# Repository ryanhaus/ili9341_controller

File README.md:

# ili9341_controller
Powered by an RP2040 and a Lattice iCE40UP5K, made by Ryan Hausmann.
Please note that everything was tested on Ubuntu running on Windows through WSL.

## Block diagram

Please note that this design has not been tested on actual hardware yet.

## Prerequisites
Run `sudo apt install make cmake gcc-arm-none-eabi libnewlib-arm-none-eabi libstdc++-arm-none-eabi-newlib build-essential clang bison flex libreadline-dev gawk tcl-dev libffi-dev git mercurial graphviz xdot pkg-config python3 libftdi-dev qtbase5-dev qtchooser qt5-qmake qtbase5-dev-tools python3-dev libboost-all-dev cmake libeigen3-dev git help2man perl python3 g++ verilator libsdl2-dev libsdl2-2.0-0`.
This is enough to do simulation with Verilator and SDL. To install the synthesis tools and the Pico SDK, run `./install_synthesis.sh`.

## Synthesis/Pico Build
Synthesis is handled by Yosys and Project Icestorm. The Pico firmware is compiled using cmake & pico-sdk.
### Building
The FPGA configuration is packaged into the RP2040 program. The `build/ili9341_controller.uf2` file can be built with `make` or `make pico`. This will compile the RP2040 program and also automatically build the FPGA configuration, with the files stored in the `build` directory. 
### Programming
On Windows, the generated uf2 file can be dragged into the Pico's drive folder.

## Simulation
Simulation has been implemented with Verilog and SDL.
### Building
To build the simulation program, run `make verilator`.
### Running
To run the simulation program, run `./build/Vili9341_controller`. The program will not do anything useful by default, but all the options can be viewed with the `--help` argument.
### Screen Simulation
To show the simulated screen output, run `./build/Vili9341_controller --screen-sim`. The `--screen-scale` argument can also be used to scale the screen, the default is 1x (240x320 px).
Below is a screenshot of a simulation with letter sprites:

## Cleaning
`make clean` will remove all build files. The dependencies will remain in the `dep` folder.

## Hardware (WIP)
All KiCad files for the PCB are in the `pcb` folder. Click [here](./pcb/sch.pdf) to download the current schematic as a PDF (`pcb/sch.pdf`).
Top view of current PCB design:

Bottom view of current PCB design:

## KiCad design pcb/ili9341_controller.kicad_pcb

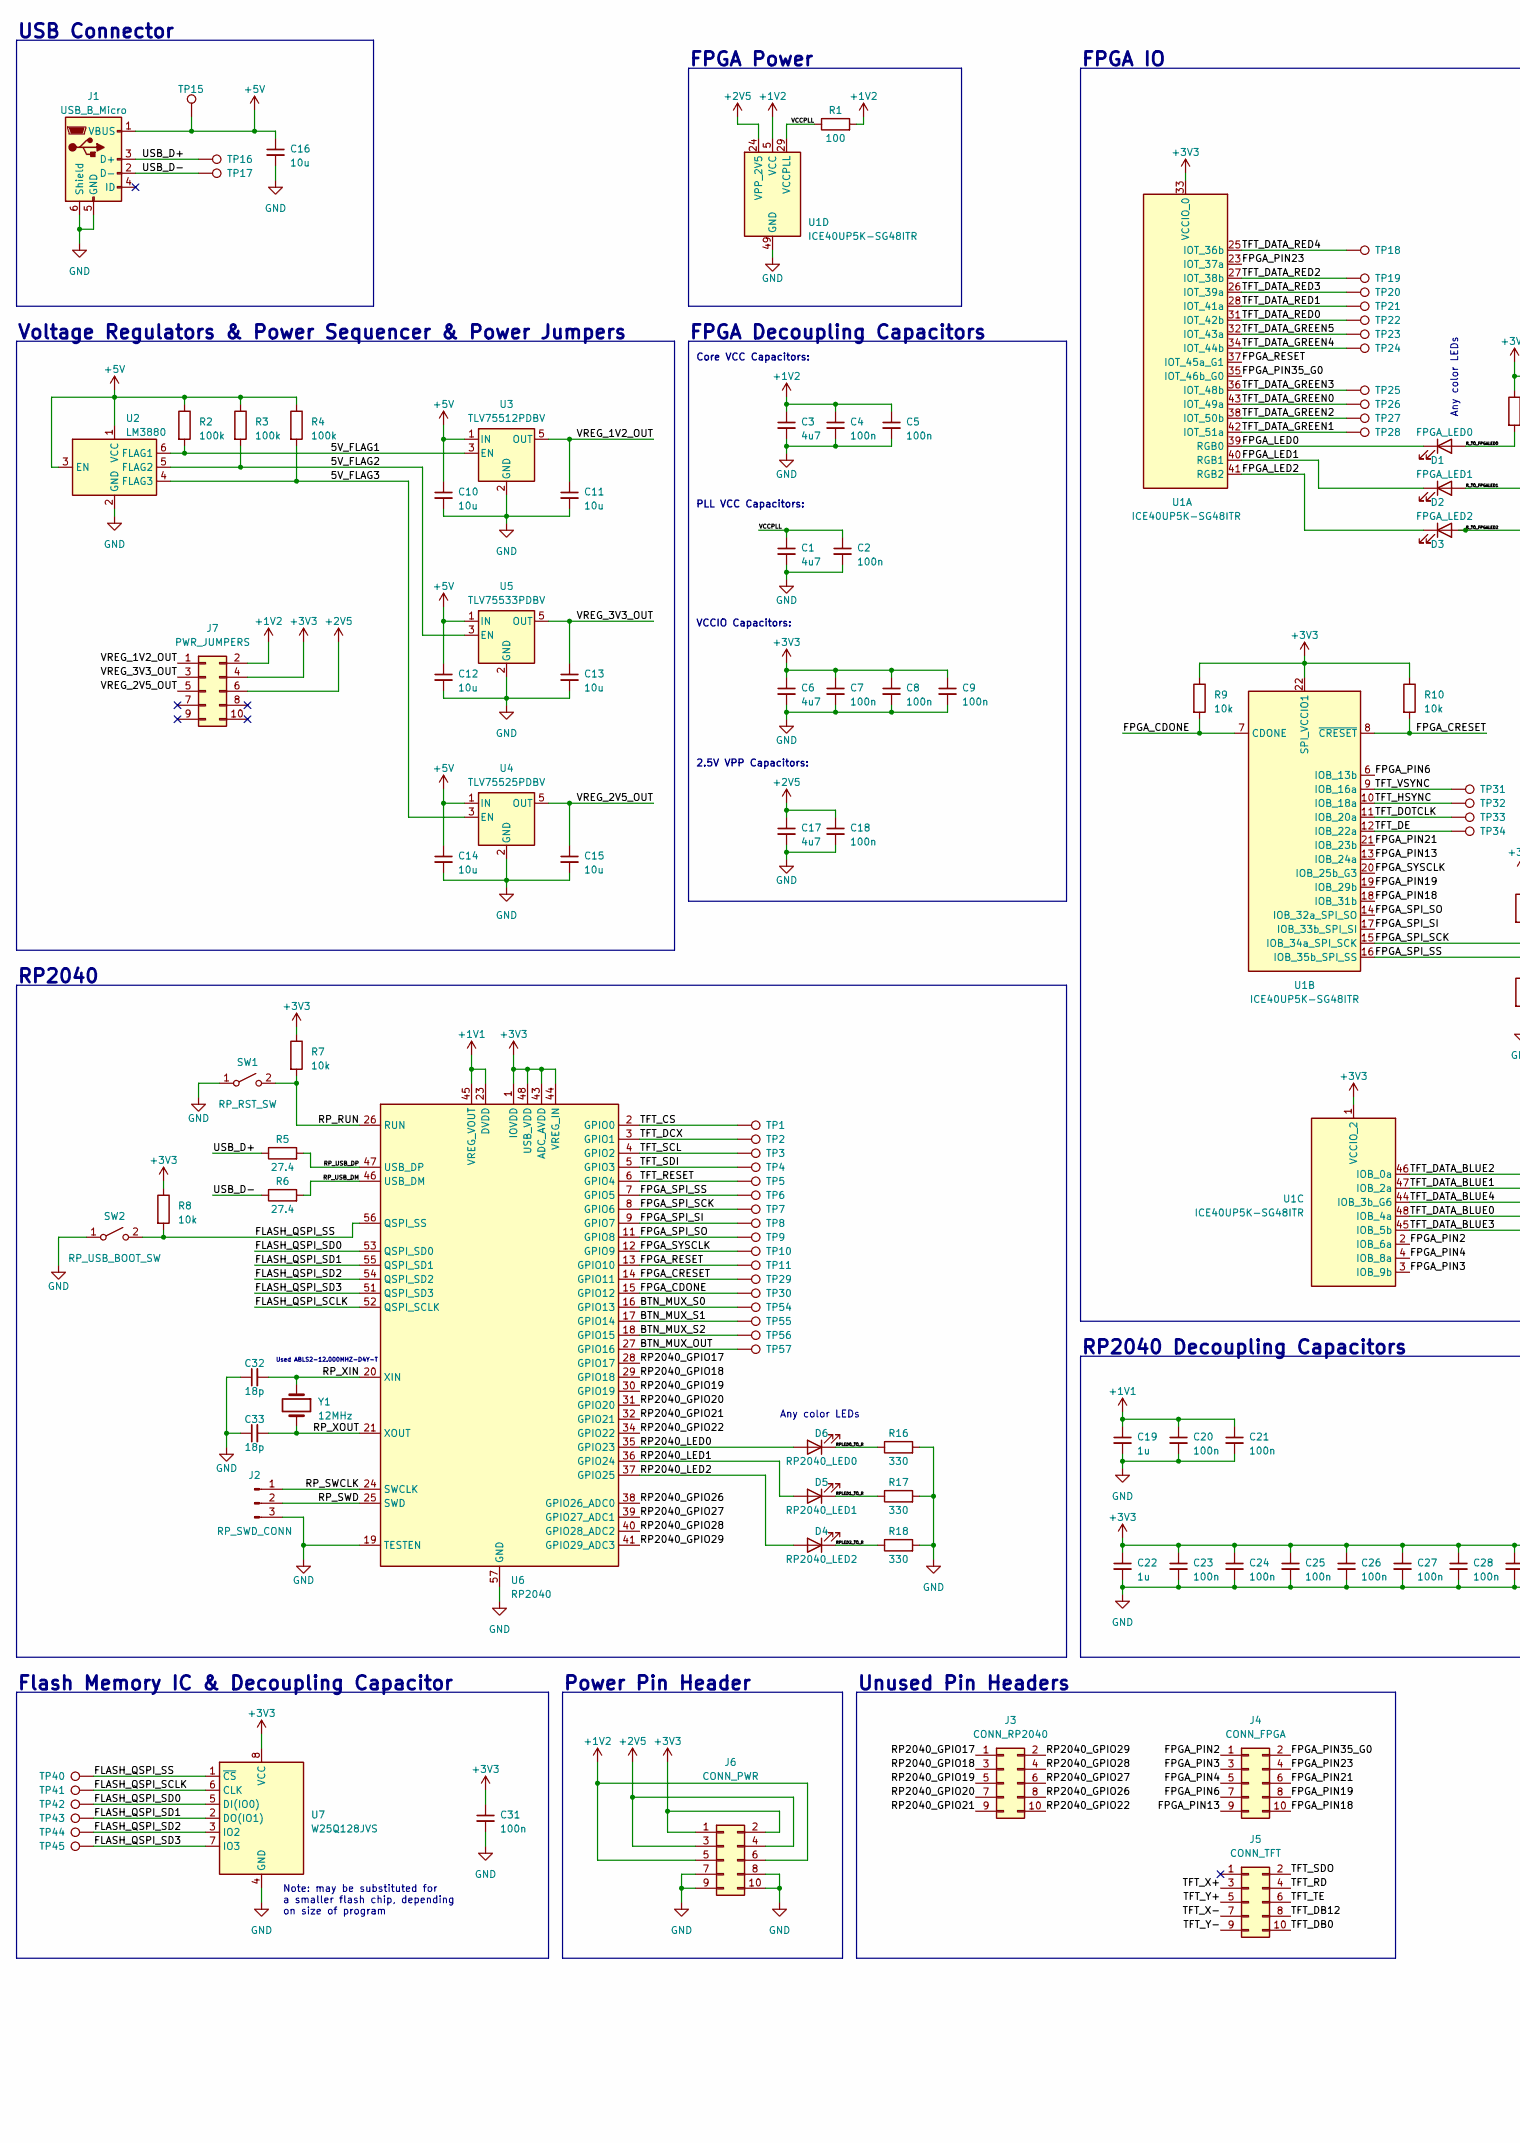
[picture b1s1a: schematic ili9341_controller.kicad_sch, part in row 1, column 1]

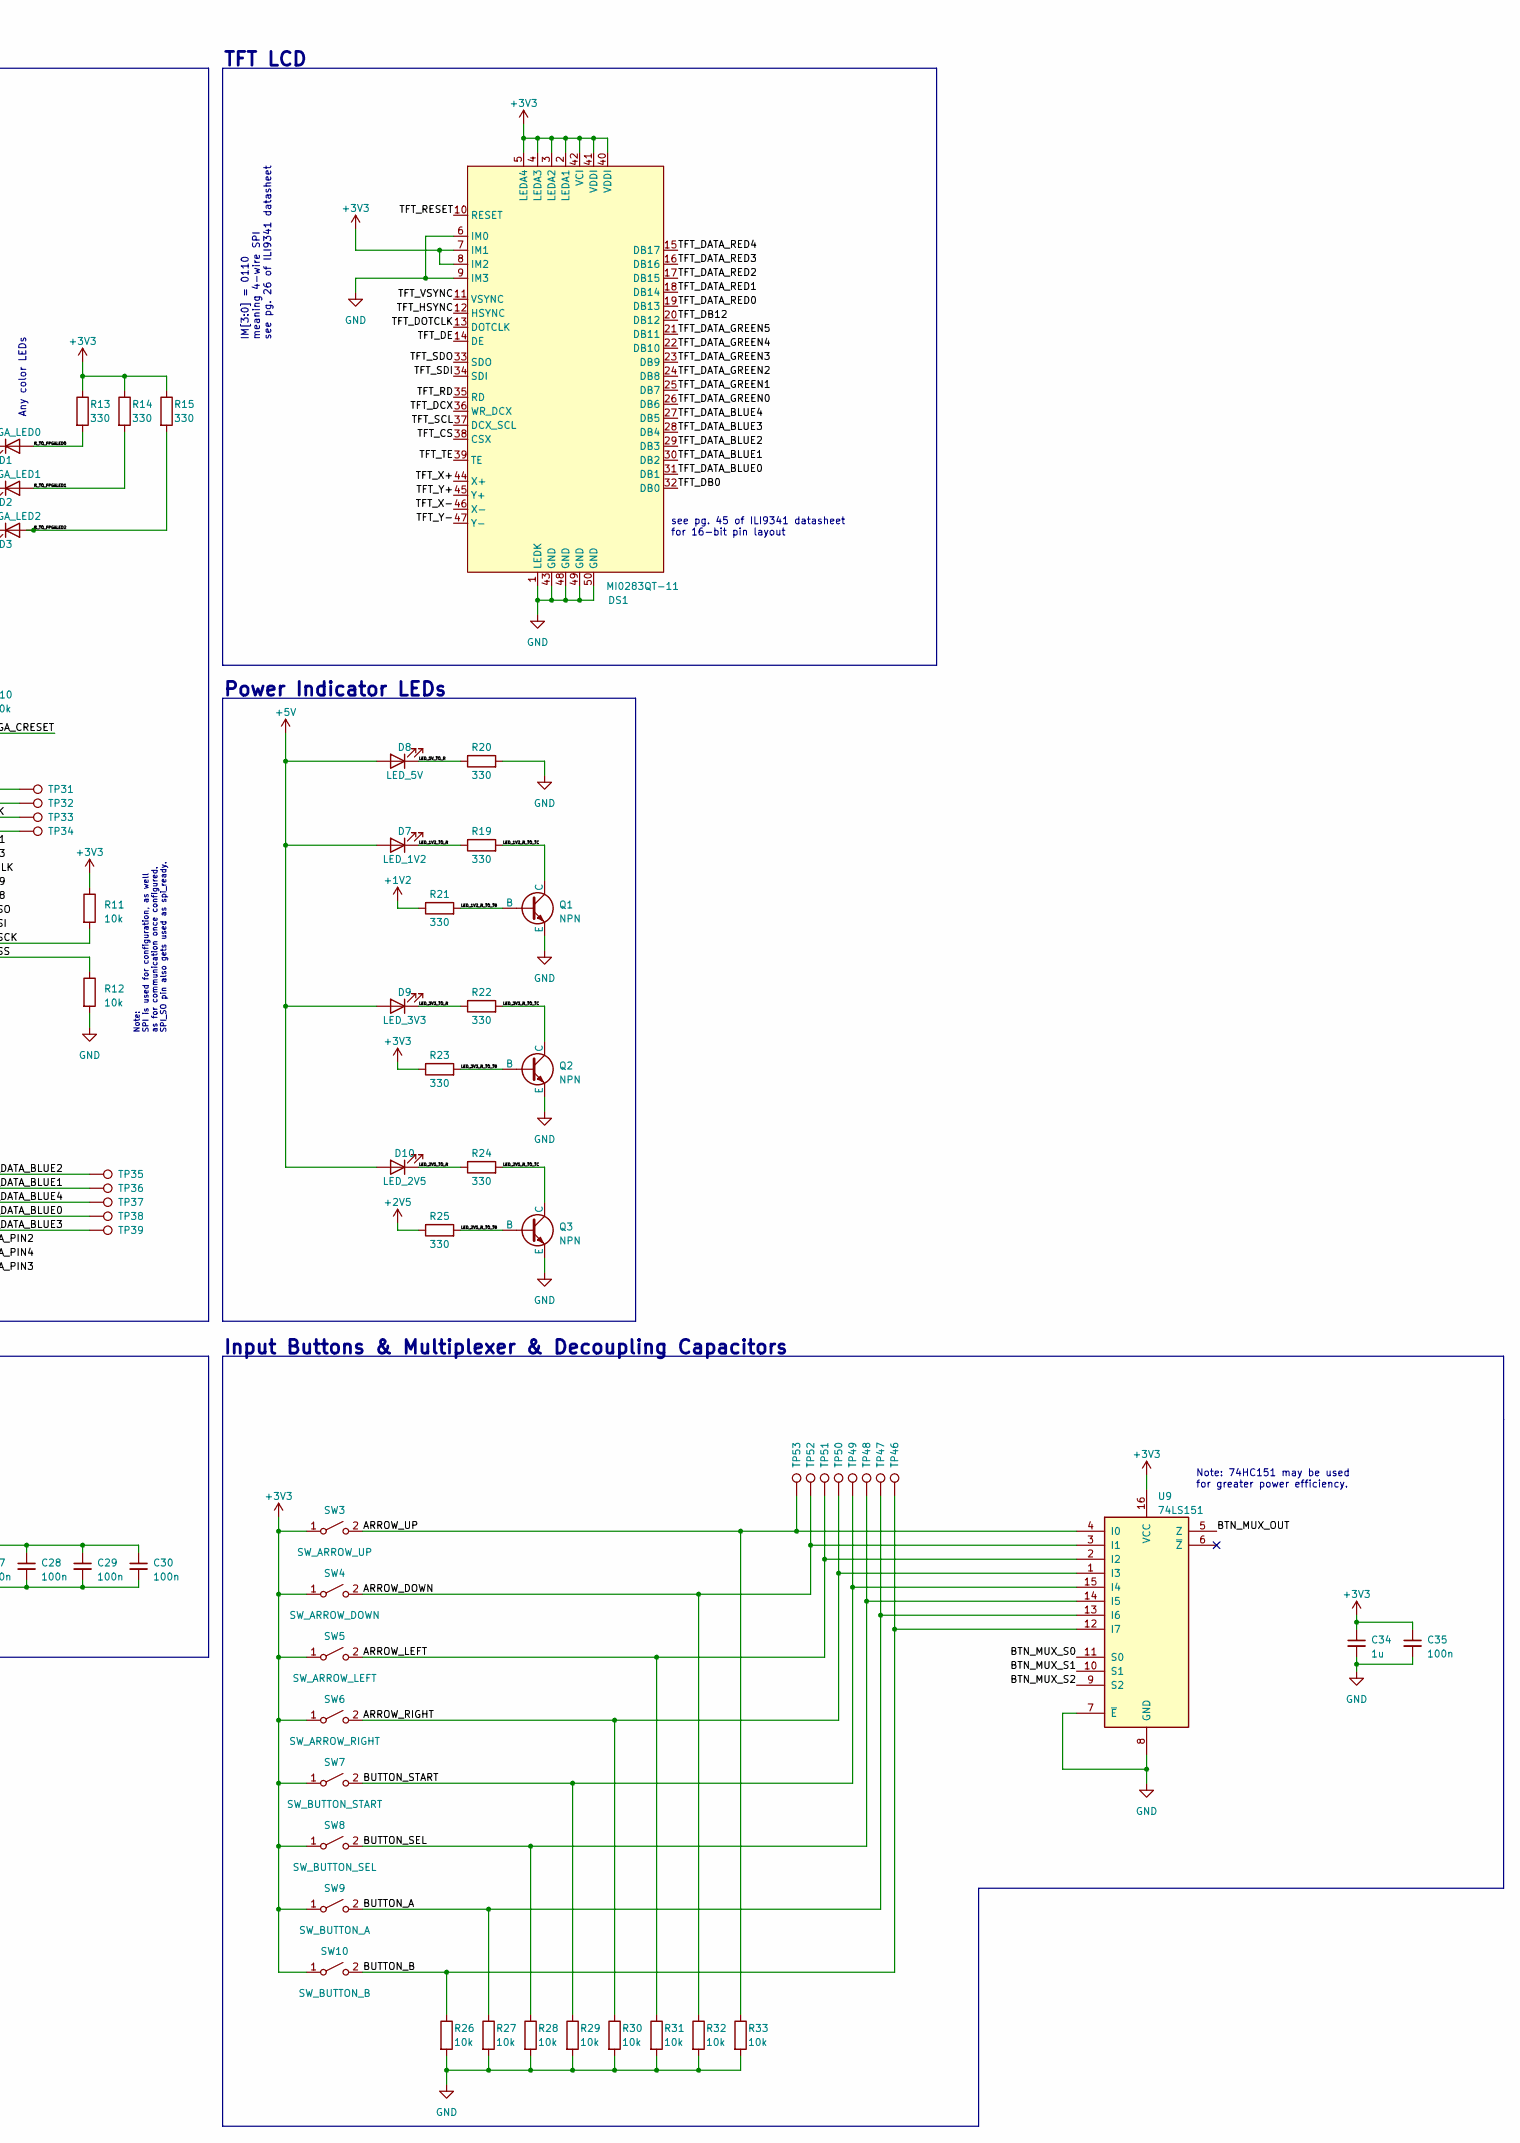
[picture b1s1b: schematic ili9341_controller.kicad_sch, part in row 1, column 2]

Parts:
C1, C3, C6, C17: 4u7; C_0603_1608Metric_Pad1.08x0.95mm_HandSolder
C2, C4, C5, C7, C8, C9, C18, C20, C21, C23, C24, C25, C26, C27, C28, C29, C30, C31, C35: 100n; C_0603_1608Metric_Pad1.08x0.95mm_HandSolder
C10, C11, C12, C13, C14, C15, C16: 10u; C_0603_1608Metric_Pad1.08x0.95mm_HandSolder
C19, C22, C34: 1u; C_0603_1608Metric_Pad1.08x0.95mm_HandSolder
C32, C33: 18p; C_0603_1608Metric_Pad1.08x0.95mm_HandSolder
D1: FPGA_LED0; LED_0603_1608Metric_Pad1.05x0.95mm_HandSolder
D2: FPGA_LED1; LED_0603_1608Metric_Pad1.05x0.95mm_HandSolder
D3: FPGA_LED2; LED_0603_1608Metric_Pad1.05x0.95mm_HandSolder
D4: RP2040_LED2; LED_0603_1608Metric_Pad1.05x0.95mm_HandSolder
D5: RP2040_LED1; LED_0603_1608Metric_Pad1.05x0.95mm_HandSolder
D6: RP2040_LED0; LED_0603_1608Metric_Pad1.05x0.95mm_HandSolder
D7: LED_1V2; LED_0603_1608Metric_Pad1.05x0.95mm_HandSolder
D8: LED_5V; LED_0603_1608Metric_Pad1.05x0.95mm_HandSolder
D9: LED_3V3; LED_0603_1608Metric_Pad1.05x0.95mm_HandSolder
D10: LED_2V5; LED_0603_1608Metric_Pad1.05x0.95mm_HandSolder
DS1: MI0283QT-11; TE_5-1734839-0_1x50-1MP_P0.5mm_Horizontal
J1: USB_B_Micro; USB_Micro-B_Molex-105017-0001
J2: RP_SWD_CONN; PinHeader_1x03_P2.54mm_Vertical
J3: CONN_RP2040; PinHeader_2x05_P2.54mm_Vertical
J4: CONN_FPGA; PinHeader_2x05_P2.54mm_Vertical
J5: CONN_TFT; PinHeader_2x05_P2.54mm_Vertical
J6: CONN_PWR; PinHeader_2x05_P2.54mm_Vertical
J7: PWR_JUMPERS; PinHeader_2x05_P2.54mm_Vertical
Q1, Q2, Q3: NPN; SOT-23-3
R1: 100; R_0603_1608Metric_Pad0.98x0.95mm_HandSolder
R2, R3, R4: 100k; R_0603_1608Metric_Pad0.98x0.95mm_HandSolder
R5, R6: 27.4; R_0603_1608Metric_Pad0.98x0.95mm_HandSolder
R7, R8, R9, R10, R11, R12, R26, R27, R28, R29, R30, R31, R32, R33: 10k; R_0603_1608Metric_Pad0.98x0.95mm_HandSolder
R13, R14, R15, R16, R17, R18, R19, R20, R21, R22, R23, R24, R25: 330; R_0603_1608Metric_Pad0.98x0.95mm_HandSolder
SW1: RP_RST_SW; SW_SPST_PTS645
SW2: RP_USB_BOOT_SW; SW_SPST_PTS645
SW3: SW_ARROW_UP; SW_SPST_PTS645
SW4: SW_ARROW_DOWN; SW_SPST_PTS645
SW5: SW_ARROW_LEFT; SW_SPST_PTS645
SW6: SW_ARROW_RIGHT; SW_SPST_PTS645
SW7: SW_BUTTON_START; SW_SPST_PTS645
SW8: SW_BUTTON_SEL; SW_SPST_PTS645
SW9: SW_BUTTON_A; SW_SPST_PTS645
SW10: SW_BUTTON_B; SW_SPST_PTS645
TP1, TP2, TP3, TP4, TP5, TP6, TP7, TP8, TP9, TP10, TP11, TP15, TP16, TP17, TP18, TP19, TP20, TP21, TP22, TP23, TP24, TP25, TP26, TP27, TP28, TP29, TP30, TP31, TP32, TP33, TP34, TP35, TP36, TP37, TP38, TP39, TP40, TP41, TP42, TP43, TP44, TP45, TP46, TP47, TP48, TP49, TP50, TP51, TP52, TP53, TP54, TP55, TP56, TP57: TestPoint; TestPoint_Pad_1.0x1.0mm
U1: ICE40UP5K-SG48ITR; QFN-48-1EP_7x7mm_P0.5mm_EP5.6x5.6mm
U2: LM3880; SOT-23-6
U3: TLV75512PDBV; SOT-23-5
U4: TLV75525PDBV; SOT-23-5
U5: TLV75533PDBV; SOT-23-5
U6: RP2040; QFN-56-1EP_7x7mm_P0.4mm_EP3.2x3.2mm
U7: W25Q128JVS; SOIC-8_5.23x5.23mm_P1.27mm
U9: 74LS151; SOIC-16_3.9x9.9mm_P1.27mm
Y1: 12MHz; XTAL_ABLS2-12.000MHZ-D4Y-T

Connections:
+1V1: C19.1, C20.1, C21.1, U6.23 (DVDD), U6.45 (VREG_VOUT), U6.50 (DVDD)
+1V2: C3.1, C4.1, C5.1, J6.5, J6.6, J7.2, R1.2, R21.1, U1.5 (VCC), U1.30 (VCC)
+2V5: C17.1, C18.1, J6.3, J6.4, J7.6, R25.1, U1.24 (VPP_2V5)
+3V3: C6.1, C7.1, C8.1, C9.1, C22.1, C23.1, C24.1, C25.1, C26.1, C27.1, C28.1, C29.1, C30.1, C31.1, C34.1, C35.1, DS1.2 (LEDA1), DS1.3 (LEDA2), DS1.4 (LEDA3), DS1.5 (LEDA4), DS1.7 (IM1), DS1.8 (IM2), DS1.40 (VDDI), DS1.41 (VDDI), DS1.42 (VCI), J6.1, J6.2, J7.4, R7.1, R8.1, R9.1, R10.1, R11.1, R13.1, R14.1, R15.1, R23.1, SW3.1 (A), SW4.1 (A), SW5.1 (A), SW6.1 (A), SW7.1 (A), SW8.1 (A), SW9.1 (A), SW10.1 (A), U1.1 (VCCIO_2), U1.22 (SPI_VCCIO1), U1.33 (VCCIO_0), U6.1 (IOVDD), U6.10 (IOVDD), U6.22 (IOVDD), U6.33 (IOVDD), U6.42 (IOVDD), U6.43 (ADC_AVDD), U6.44 (VREG_IN), U6.48 (USB_VDD), U6.49 (IOVDD), U7.8 (VCC), U9.16 (VCC)
+5V: C10.1, C12.1, C14.1, C16.1, D7.2 (A), D8.2 (A), D9.2 (A), D10.2 (A), J1.1 (VBUS), R2.1, R3.1, R4.1, TP15.1, U2.1 (VCC), U2.3 (EN), U3.1 (IN), U4.1 (IN), U5.1 (IN)
/5V_FLAG1: R2.2, U2.6 (FLAG1), U3.3 (EN)
/5V_FLAG2: R3.2, U2.5 (FLAG2), U5.3 (EN)
/5V_FLAG3: R4.2, U2.4 (FLAG3), U4.3 (EN)
/ARROW_DOWN: R32.1, SW4.2 (B), TP52.1, U9.3 (I1)
/ARROW_LEFT: R31.1, SW5.2 (B), TP51.1, U9.2 (I2)
/ARROW_RIGHT: R30.1, SW6.2 (B), TP50.1, U9.1 (I3)
/ARROW_UP: R33.1, SW3.2 (B), TP53.1, U9.4 (I0)
/BTN_MUX_OUT: TP57.1, U6.27 (GPIO16), U9.5 (Z)
/BTN_MUX_S0: TP54.1, U6.16 (GPIO13), U9.11 (S0)
/BTN_MUX_S1: TP55.1, U6.17 (GPIO14), U9.10 (S1)
/BTN_MUX_S2: TP56.1, U6.18 (GPIO15), U9.9 (S2)
/BUTTON_A: R27.1, SW9.2 (B), TP47.1, U9.13 (I6)
/BUTTON_B: R26.1, SW10.2 (B), TP46.1, U9.12 (I7)
/BUTTON_SEL: R28.1, SW8.2 (B), TP48.1, U9.14 (I5)
/BUTTON_START: R29.1, SW7.2 (B), TP49.1, U9.15 (I4)
/FLASH_QSPI_SCLK: TP41.1, U6.52 (QSPI_SCLK), U7.6 (CLK)
/FLASH_QSPI_SD0: TP42.1, U6.53 (QSPI_SD0), U7.5 (DI(IO0))
/FLASH_QSPI_SD1: TP43.1, U6.55 (QSPI_SD1), U7.2 (DO(IO1))
/FLASH_QSPI_SD2: TP44.1, U6.54 (QSPI_SD2), U7.3 (IO2)
/FLASH_QSPI_SD3: TP45.1, U6.51 (QSPI_SD3), U7.7 (IO3)
/FLASH_QSPI_SS: R8.2, SW2.2 (B), TP40.1, U6.56 (QSPI_SS), U7.1 (~CS)
/FPGA_CDONE: R9.2, TP30.1, U1.7 (CDONE), U6.15 (GPIO12)
/FPGA_CRESET: R10.2, TP29.1, U1.8 (~CRESET), U6.14 (GPIO11)
/FPGA_LED0: D1.1 (K), U1.39 (RGB0)
/FPGA_LED1: D2.1 (K), U1.40 (RGB1)
/FPGA_LED2: D3.1 (K), U1.41 (RGB2)
/FPGA_PIN2: J4.1, U1.2 (IOB_6a)
/FPGA_PIN3: J4.3, U1.3 (IOB_9b)
/FPGA_PIN4: J4.5, U1.4 (IOB_8a)
/FPGA_PIN6: J4.7, U1.6 (IOB_13b)
/FPGA_PIN13: J4.9, U1.13 (IOB_24a)
/FPGA_PIN18: J4.10, U1.18 (IOB_31b)
/FPGA_PIN19: J4.8, U1.19 (IOB_29b)
/FPGA_PIN21: J4.6, U1.21 (IOB_23b)
/FPGA_PIN23: J4.4, U1.23 (IOT_37a)
/FPGA_PIN35_G0: J4.2, U1.35 (IOT_46b_G0)
/FPGA_RESET: TP11.1, U1.37 (IOT_45a_G1), U6.13 (GPIO10)
/FPGA_SPI_SCK: R11.2, TP7.1, U1.15 (IOB_34a_SPI_SCK), U6.8 (GPIO6)
/FPGA_SPI_SI: TP8.1, U1.17 (IOB_33b_SPI_SI), U6.9 (GPIO7)
/FPGA_SPI_SO: TP9.1, U1.14 (IOB_32a_SPI_SO), U6.11 (GPIO8)
/FPGA_SPI_SS: R12.1, TP6.1, U1.16 (IOB_35b_SPI_SS), U6.7 (GPIO5)
/FPGA_SYSCLK: TP10.1, U1.20 (IOB_25b_G3), U6.12 (GPIO9)
/LED_1V2_R_TO_TB: Q1.2 (B), R21.2
/LED_1V2_R_TO_TC: Q1.1 (C), R19.2
/LED_1V2_TO_R: D7.1 (K), R19.1
/LED_2V5_R_TO_TB: Q3.2 (B), R25.2
/LED_2V5_R_TO_TC: Q3.1 (C), R24.2
/LED_2V5_TO_R: D10.1 (K), R24.1
/LED_3V3_R_TO_TB: Q2.2 (B), R23.2
/LED_3V3_R_TO_TC: Q2.1 (C), R22.2
/LED_3V3_TO_R: D9.1 (K), R22.1
/LED_5V_TO_R: D8.1 (K), R20.1
/RP2040_GPIO17: J3.1, U6.28 (GPIO17)
/RP2040_GPIO18: J3.3, U6.29 (GPIO18)
/RP2040_GPIO19: J3.5, U6.30 (GPIO19)
/RP2040_GPIO20: J3.7, U6.31 (GPIO20)
/RP2040_GPIO21: J3.9, U6.32 (GPIO21)
/RP2040_GPIO22: J3.10, U6.34 (GPIO22)
/RP2040_GPIO26: J3.8, U6.38 (GPIO26_ADC0)
/RP2040_GPIO27: J3.6, U6.39 (GPIO27_ADC1)
/RP2040_GPIO28: J3.4, U6.40 (GPIO28_ADC2)
/RP2040_GPIO29: J3.2, U6.41 (GPIO29_ADC3)
/RP2040_LED0: D6.2 (A), U6.35 (GPIO23)
/RP2040_LED1: D5.2 (A), U6.36 (GPIO24)
/RP2040_LED2: D4.2 (A), U6.37 (GPIO25)
/RPLED0_TO_R: D6.1 (K), R16.1
/RPLED1_TO_R: D5.1 (K), R17.1
/RPLED2_TO_R: D4.1 (K), R18.1
/RP_RUN: R7.2, SW1.2 (B), U6.26 (RUN)
/RP_SWCLK: J2.1, U6.24 (SWCLK)
/RP_SWD: J2.2, U6.25 (SWD)
/RP_USB_DM: R6.2, U6.46 (USB_DM)
/RP_USB_DP: R5.2, U6.47 (USB_DP)
/RP_XIN: C32.2, U6.20 (XIN), Y1.1
/RP_XOUT: C33.2, U6.21 (XOUT), Y1.2
/R_TO_FPGALED0: D1.2 (A), R13.2
/R_TO_FPGALED1: D2.2 (A), R14.2
/R_TO_FPGALED2: D3.2 (A), R15.2
/TFT_CS: DS1.38 (CSX), TP1.1, U6.2 (GPIO0)
/TFT_DATA_BLUE0: DS1.31 (DB1), TP38.1, U1.48 (IOB_4a)
/TFT_DATA_BLUE1: DS1.30 (DB2), TP36.1, U1.47 (IOB_2a)
/TFT_DATA_BLUE2: DS1.29 (DB3), TP35.1, U1.46 (IOB_0a)
/TFT_DATA_BLUE3: DS1.28 (DB4), TP39.1, U1.45 (IOB_5b)
/TFT_DATA_BLUE4: DS1.27 (DB5), TP37.1, U1.44 (IOB_3b_G6)
/TFT_DATA_GREEN0: DS1.26 (DB6), TP26.1, U1.43 (IOT_49a)
/TFT_DATA_GREEN1: DS1.25 (DB7), TP28.1, U1.42 (IOT_51a)
/TFT_DATA_GREEN2: DS1.24 (DB8), TP27.1, U1.38 (IOT_50b)
/TFT_DATA_GREEN3: DS1.23 (DB9), TP25.1, U1.36 (IOT_48b)
/TFT_DATA_GREEN4: DS1.22 (DB10), TP24.1, U1.34 (IOT_44b)
/TFT_DATA_GREEN5: DS1.21 (DB11), TP23.1, U1.32 (IOT_43a)
/TFT_DATA_RED0: DS1.19 (DB13), TP22.1, U1.31 (IOT_42b)
/TFT_DATA_RED1: DS1.18 (DB14), TP21.1, U1.28 (IOT_41a)
/TFT_DATA_RED2: DS1.17 (DB15), TP19.1, U1.27 (IOT_38b)
/TFT_DATA_RED3: DS1.16 (DB16), TP20.1, U1.26 (IOT_39a)
/TFT_DATA_RED4: DS1.15 (DB17), TP18.1, U1.25 (IOT_36b)
/TFT_DB0: DS1.32 (DB0), J5.10
/TFT_DB12: DS1.20 (DB12), J5.8
/TFT_DCX: DS1.36 (WR_DCX), TP2.1, U6.3 (GPIO1)
/TFT_DE: DS1.14 (DE), TP34.1, U1.12 (IOB_22a)
/TFT_DOTCLK: DS1.13 (DOTCLK), TP33.1, U1.11 (IOB_20a)
/TFT_HSYNC: DS1.12 (HSYNC), TP32.1, U1.10 (IOB_18a)
/TFT_RD: DS1.35 (RD), J5.4
/TFT_RESET: DS1.10 (RESET), TP5.1, U6.6 (GPIO4)
/TFT_SCL: DS1.37 (DCX_SCL), TP3.1, U6.4 (GPIO2)
/TFT_SDI: DS1.34 (SDI), TP4.1, U6.5 (GPIO3)
/TFT_SDO: DS1.33 (SDO), J5.2
/TFT_TE: DS1.39 (TE), J5.6
/TFT_VSYNC: DS1.11 (VSYNC), TP31.1, U1.9 (IOB_16a)
/TFT_X+: DS1.44 (X+), J5.3
/TFT_X-: DS1.46 (X-), J5.7
/TFT_Y+: DS1.45 (Y+), J5.5
/TFT_Y-: DS1.47 (Y-), J5.9
/USB_D+: J1.3 (D+), R5.1, TP16.1
/USB_D-: J1.2 (D-), R6.1, TP17.1
/VCCPLL: C1.1, C2.1, R1.1, U1.29 (VCCPLL)
/VREG_1V2_OUT: C11.1, J7.1, U3.5 (OUT)
/VREG_2V5_OUT: C15.1, J7.5, U4.5 (OUT)
/VREG_3V3_OUT: C13.1, J7.3, U5.5 (OUT)
GND: C1.2, C2.2, C3.2, C4.2, C5.2, C6.2, C7.2, C8.2, C9.2, C10.2, C11.2, C12.2, C13.2, C14.2, C15.2, C16.2, C17.2, C18.2, C19.2, C20.2, C21.2, C22.2, C23.2, C24.2, C25.2, C26.2, C27.2, C28.2, C29.2, C30.2, C31.2, C32.1, C33.1, C34.2, C35.2, DS1.1 (LEDK), DS1.6 (IM0), DS1.9 (IM3), DS1.43 (GND), DS1.48 (GND), DS1.49 (GND), DS1.50 (GND), J1.5 (GND), J1.6 (Shield), J2.3, J6.7, J6.8, J6.9, J6.10, Q1.3 (E), Q2.3 (E), Q3.3 (E), R12.2, R16.2, R17.2, R18.2, R20.2, R26.2, R27.2, R28.2, R29.2, R30.2, R31.2, R32.2, R33.2, SW1.1 (A), SW2.1 (A), U1.49 (GND), U2.2 (GND), U3.2 (GND), U4.2 (GND), U5.2 (GND), U6.19 (TESTEN), U6.57 (GND), U7.4 (GND), U9.7 (~E), U9.8 (GND)

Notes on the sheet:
FPGA Decoupling Capacitors
RP2040
Note: SPI is used for configuration, as well as for communication once configured. SPI_SO pin also gets used as spi_ready.
USB Connector
see pg. 45 of ILI9341 datasheet for 16-bit pin layout
Power Pin Header
FPGA IO
Input Buttons & Multiplexer & Decoupling Capacitors
Flash Memory IC & Decoupling Capacitor
Any color LEDs
Used ABLS2-12.000MHZ-D4Y-T
PLL VCC Capacitors:
Core VCC Capacitors:
TFT LCD
VCCIO Capacitors:
2.5V VPP Capacitors:
Unused Pin Headers
Note: may be substituted for a smaller flash chip, depending on size of program
Note: 74HC151 may be used for greater power efficiency.
FPGA Power
Power Indicator LEDs
Voltage Regulators & Power Sequencer & Power Jumpers
RP2040 Decoupling Capacitors
IM[3:0] = 0110 meaning 4-wire SPI see pg. 26 of ILI9341 datasheet

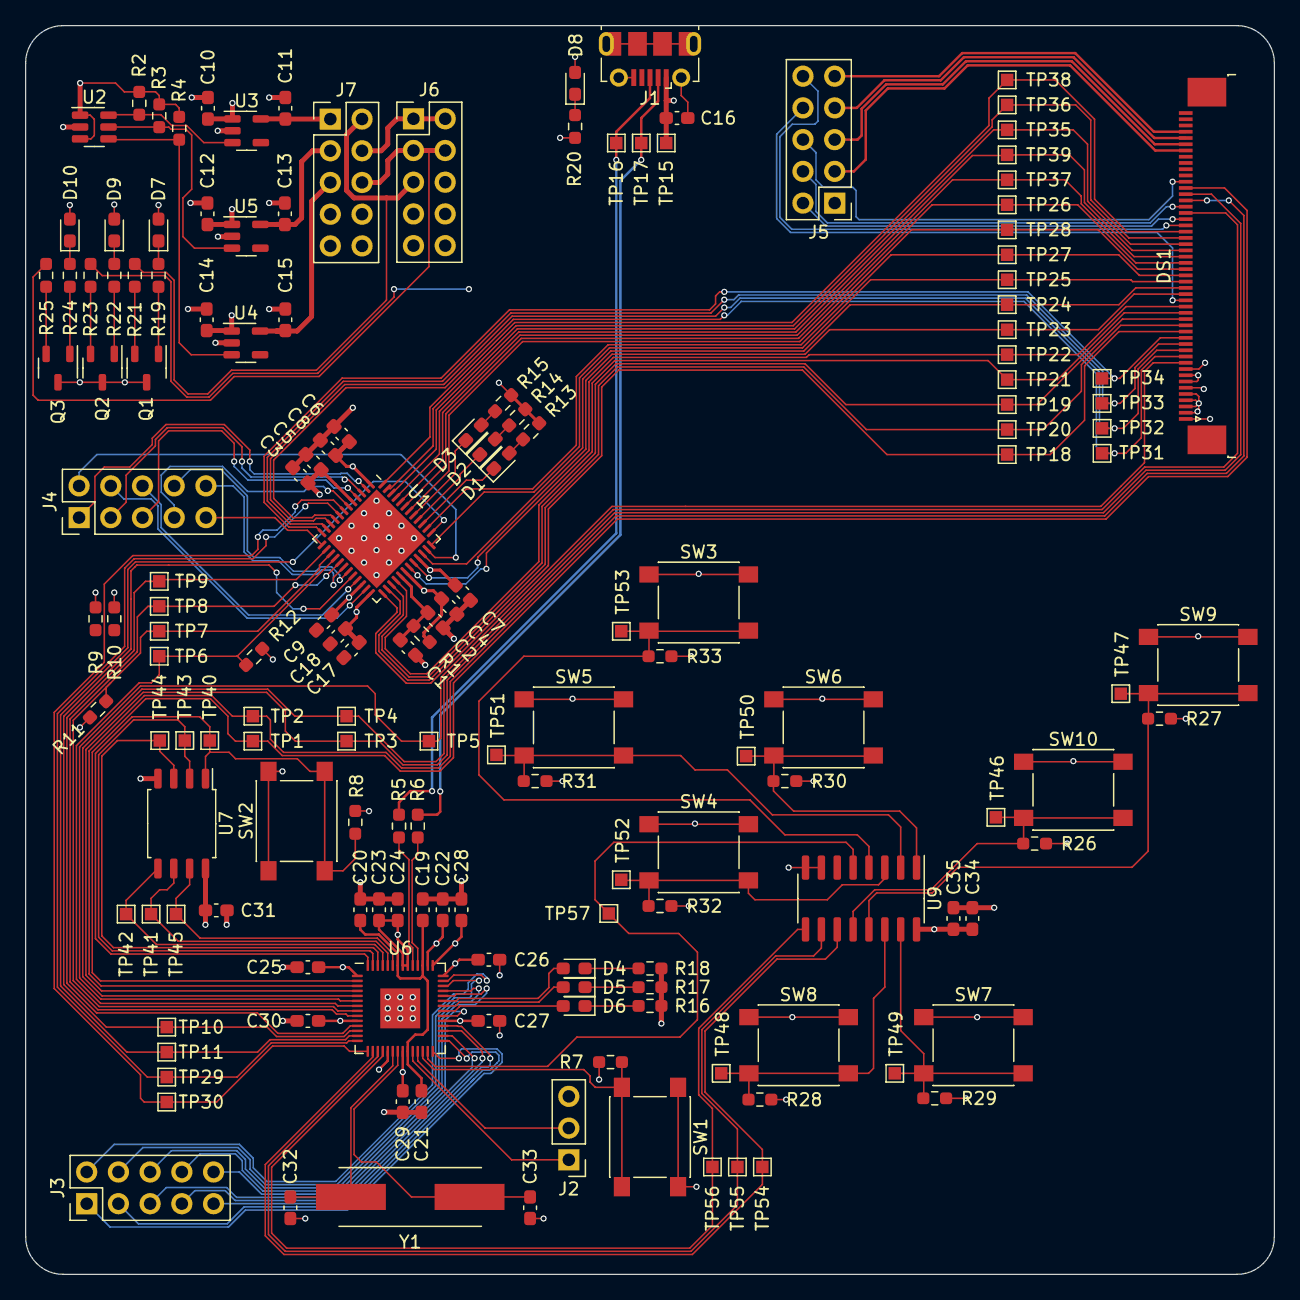
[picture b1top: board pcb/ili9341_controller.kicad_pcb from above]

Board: 4 copper layers, 100.0 x 100.0 mm, 162 parts (0 on the bottom side), 124 nets.

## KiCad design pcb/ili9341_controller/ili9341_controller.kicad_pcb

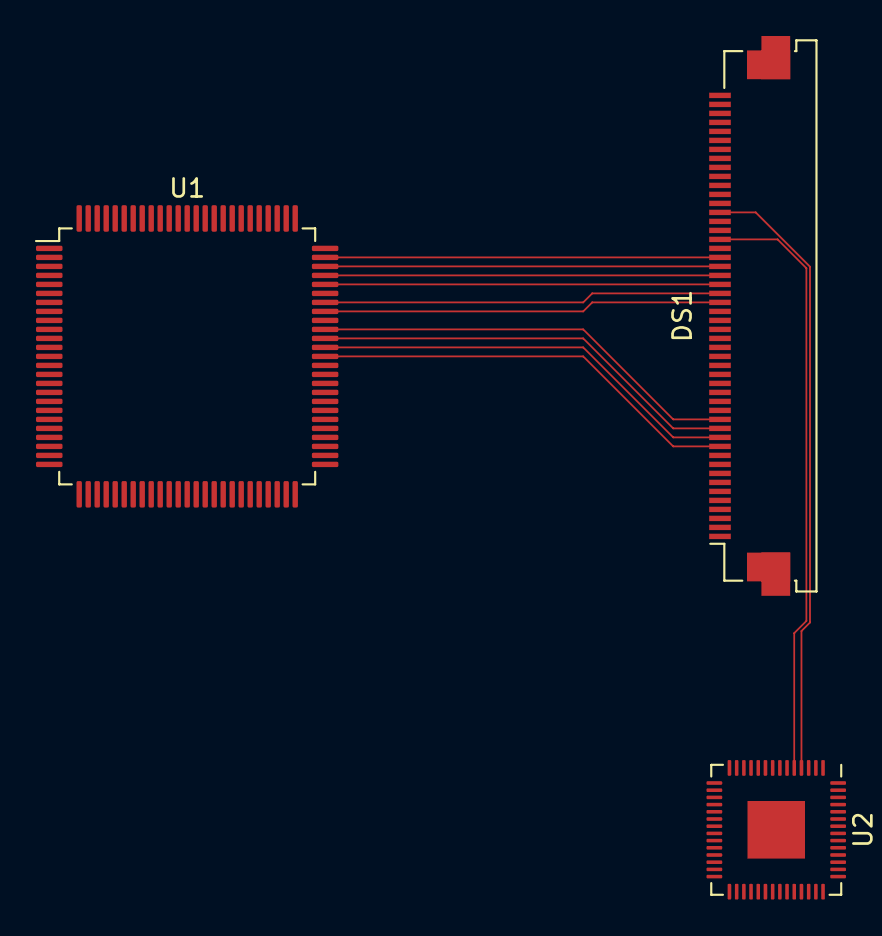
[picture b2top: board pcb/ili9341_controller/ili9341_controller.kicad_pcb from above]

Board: 2 copper layers, 3 parts (0 on the bottom side), 20 nets.

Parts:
DS1: Molex_54132-5033_1x50-1MP_P0.5mm_Horizontal
U1: ICE40HX1K-VQ100; TQFP-100_14x14mm_P0.5mm
U2: RP2040; QFN-56-1EP_7x7mm_P0.4mm_EP3.2x3.2mm

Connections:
+1V1: U2.23 (DVDD), U2.45 (VREG_VOUT), U2.50 (DVDD)
+1V2: U1.11 (VCC), U1.35 (VCC), U1.61 (VCC), U1.77 (VCC)
+3V3: DS1.2 (LEDA1), DS1.3 (LEDA2), DS1.4 (LEDA3), DS1.5 (LEDA4), DS1.40 (VDDI), DS1.41 (VDDI), DS1.42 (VCI), U1.6 (VCCIO_3), U1.14 (VCCIO_3), U1.22 (VCC_IO3), U1.31 (VCCIO_2), U1.38 (VCCIO_2), U1.50 (VCC_SPI), U1.58 (VCCIO_1), U1.67 (VCCIO_1), U1.88 (VCCIO_0), U1.92 (VCCIO_0), U2.1 (IOVDD), U2.10 (IOVDD), U2.22 (IOVDD), U2.26 (RUN), U2.33 (IOVDD), U2.42 (IOVDD), U2.43 (ADC_AVDD), U2.44 (VREG_IN), U2.48 (USB_VDD), U2.49 (IOVDD)
/FPGA_RESET: U1.15 (IOL_7A_GBIN6), U2.7 (GPIO5)
/TFT_CSX: DS1.38 (CSX), U2.2 (GPIO0)
/TFT_DB0: DS1.32 (DB0), U1.74 (IOR_72)
/TFT_DB1: DS1.31 (DB1), U1.73 (IOR_71)
/TFT_DB2: DS1.30 (DB2), U1.72 (IOR_70)
/TFT_DB3: DS1.29 (DB3), U1.71 (IOR_69)
/TFT_DB4: DS1.28 (DB4), U1.69 (IOR_68)
/TFT_DB5: DS1.27 (DB5), U1.68 (IOR_67)
/TFT_DCX_SCL: DS1.37 (DCX_SCL), U2.4 (GPIO2)
/TFT_DE: DS1.14 (DE), U1.66 (IOR_65)
/TFT_DOTCLK: DS1.13 (DOTCLK), U1.65 (IOR_64)
/TFT_HSYNC: DS1.12 (HSYNC), U1.64 (IOR_63)
/TFT_RESET: DS1.10 (RESET), U2.6 (GPIO4)
/TFT_SDI: DS1.34 (SDI), U2.5 (GPIO3)
/TFT_VSYNC: DS1.11 (VSYNC), U1.63 (IOR_61_GBIN2)
/TFT_WR_DCX: DS1.36 (WR_DCX), U2.3 (GPIO1)
GND: DS1.1 (LEDK), DS1.43 (GND), DS1.48 (GND), DS1.49 (GND), DS1.50 (GND), U1.5 (GND), U1.17 (GND), U1.23 (GND), U1.32 (GND), U1.39 (GND), U1.47 (GND), U1.55 (GND), U1.70 (GND), U1.84 (GND), U1.98 (GND), U2.57 (GND)

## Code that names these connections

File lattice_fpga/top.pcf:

set_io sysclk 44
set_io tft_dotclk 35
set_io reset 37
set_io spi_sck 43
set_io spi_sda 42
set_io spi_ready 45
set_io tft_hsync 36
set_io tft_vsync 34
set_io tft_data_enable 32
set_io tft_data[0] 31
set_io tft_data[1] 28
set_io tft_data[2] 27
set_io tft_data[3] 26
set_io tft_data[4] 25
set_io tft_data[5] 23
set_io tft_data[6] 21
set_io tft_data[7] 20
set_io tft_data[8] 19
set_io tft_data[9] 18
set_io tft_data[10] 13
set_io tft_data[11] 12
set_io tft_data[12] 11
set_io tft_data[13] 10
set_io tft_data[14] 9
set_io tft_data[15] 6

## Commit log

2023-11-14 remove pico build files
2023-11-14 remove unnecessary vivado files
2023-11-17 proper building, verilator simulation
2023-11-17 fixed verilator/initialization & changed video test
    changed the test display from a solid red color to a red/green gradient, also fixed a bug in the verilator sim that caused the output to be flipped horizontally. also changed it so that the video out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
2023-11-19 separated sync signals from video generation, fixed sim clock error, changed makefile
2023-11-19 fix makefile for verilator
2023-11-19 remove unnecessary dependencies, clean up makefile
2023-11-21 convert to 16-bit, 3 transfers/px
    note: not tested on hardware yet, but sim output seems right
    converting to 16 bits per pixel (565 RGB) and 3 transfers per pixel to make implementing memory in the future easier, also to reduce number of wires needed (data lines go from 18 wires to 6 wires), s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
2023-11-27 fix fpga errors
    also now officially tested/verified on actual hardware, not just simulation
2023-11-27 fix to only use 6 wires for data line
    as opposed to 18
2023-11-27 change verilator code
    more readable & more similar to how the actual hardware functions
2023-11-27 change verilator
    changed verilator to c instead of c++ for consistency w/ pico
2023-11-28 remove unnecessary SDL include
2023-11-28 FPGA SPI communication
    the test is not frame-synced, so its a little jittery, but the proof of concept is there--the next steps are to add a sprite engine
2023-11-28 update verilator to test spi
2023-11-29 fix spi
    reversed shift register direction, changed the test to be a pulsating red color
2023-11-29 fix comment
2023-11-29 memory writing and reading
    write from SPI, read during display period
    currently, reading an 8-bit value from memory depending on the pixel position and setting the red component to the first 6 bits of that value
    the pico is just feeding in random write locations and random values
2023-12-01 improve verilator sim, add SPI FIFO
    verilator can now output a trace dump file (controlled by the --trace argument when running the executable), and also added a FIFO for the SPI input to allow data transfer to happen during a memory r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
2023-12-04 test out higher SPI frequency
    SPI set to 62.5MHz, the highest supported by the RP2040 w/o overclocking
2023-12-04 improve FIFO
    however, it is not working that well. might switch back to how it was before w/o the FIFO, as that worked better
2023-12-06 vastly improve verilator, some issues remain
    verilator sim is able to handle multiple concurrent clocks now, which will allow for the testing of concurrent SPI data and TFT data
    also fixed some minor issues with the verilog
2023-12-07 fixed issues on verilator
2023-12-07 convert everything to clocked logic, improve verilator output
2023-12-07 remove verilator frame rate calculations
2023-12-08 verilog overhaul
    got everything working nicely, there are just some instances of occasionally flickering pixels on actual hardware, but i believe that this can be attributed to the timing with the spi
2023-12-08 increase fifo size, decrease spi speed
2023-12-08 add code to verify the framebuffer in verilator
    to make sure it is exactly as expected
2023-12-10 add necessary module for USB-UART communication
    currently non-implemented, but the module is there
2023-12-11 patch UART
    worked in simulation, but not on actual hardware. currently also temporarily switched the UART output to a GPIO pin since i couldn't get the on-board USB-UART bridge working, but hopefully i can soon
2023-12-11 change pico firmware to also reset FPGA as well as TFT
    also made it wait until the SPI is ready, instead of waiting 10 frames like before
2023-12-11 fix an issue with starting
    sometimes, the fpga would not start up if it was initialized before the tft
2023-12-13 start kicad design
    for the actual pcb design, I think I am going to switch to using a Lattice ICE40HX1K-VQ100 for its availability in hand-solderable packaging, and also open-source tools available for synthesis/flashi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
2023-12-13 add in chips with capacitors to schematic
2023-12-15 update pcb, begin adding in support for lattice fpga
2023-12-19 add in ability to configure ICE40HX1K from pico
    written according to FPGA-TN-02001, untested on actual hardware
2023-12-28 begin switch from HX1K to UP5K
2023-12-28 remove unnecessary include in verilog for verilator
2023-12-28 improve lattice verilator to support SDL-based screen simulation
2023-12-28 fix lattice memory handling
2023-12-28 add readme and block diagram for lattice
2023-12-31 add controllable verilator SPI, fix memory writing issues
    verilator SPI now sends pre-programmed data, also fixed an oversight with the memory writing from the SPI FIFO
2023-12-31 move files to prioritize the ice40up5k version over the xilinx version
2023-12-31 add script to install all prerequisites
2024-01-01 separate simulation dependencies from synthesis dependencies
2024-01-02 fix sdl rendering issues
2024-01-02 add white background to block diagram
2024-01-02 change the spi sim to use the queue class instead of doing it manually
2024-01-02 sim: add ability to 'upload' custom sprites easier through spi
2024-01-02 add ability to resize simulation screen; add screenshot of output to readme
2024-01-05 add file for manually inferring block ram
2024-01-05 add module for chaining multiple bram modules together by their addresses
2024-01-05 change sprites to use a color palette
    each sprite has 4x16-bit color palette and each pixel is 2 bits, as opposed to each pixel being its own 16-bit color
2024-01-05 fix issues with tiles
2024-01-05 make uploading sprites w/ color palette easier
2024-01-05 make sprites go left -> right
2024-01-06 add ability to generate sprites from a bitmap for sim
2024-01-08 create files for the PCB project (kicad)
2024-01-08 update gitignore for pcb
2024-01-10 set up power on pcb
2024-01-10 update power; add symbols for RP2040 & the TFT LCD
2024-01-14 add power symbols for rp2040 & tft lcd; add capacitors for rp2040
2024-01-14 organize schematic
2024-01-14 add rp2040 reset/boot switches; set up flash memory; add usb connection to rp2040
2024-01-14 finish connections to rp2040 (besides gpios)
2024-01-14 clarify crystal oscillator model
2024-01-15 add labels to TFT LCD in pcb
2024-01-18 resolve combinatorial loop
2024-01-18 assign FPGA pins in pcb, update yosys pin configuration file to reflect pcb design
2024-01-19 add configuration connections for fpga to rp2040
2024-01-21 add pull up and pull downs for configuration pins
2024-01-21 add user-usable LEDs and power indicator LEDs
2024-01-21 add headers for unused pins
2024-01-21 fix unconnected pins
2024-01-21 switch to use TLV755P linear regulators
2024-01-22 add test points to all unexposed pins
    also connected CRESET and CDONE to the RP2040, since i apparently forgot to do that
2024-01-22 add power pin header
2024-01-23 add input buttons
2024-01-23 add power jumper headers
    for current measurement & voltage verification
2024-01-23 replace power connector with 02x05 instead of 02x04
2024-01-23 assign (tentative) footprints to every component
2024-01-23 create pcb file, add 3d models to all components
    the 50 pin FPC connector 3d model was swapped with a 25-pin one (due to a lack of a 50 pin one), but the sizes of the models are the same and that's all that really matters
2024-01-23 add footprint for crystal
2024-01-23 add 3d models for transistors
2024-01-24 place components on pcb in groups
2024-01-25 place and route out all components
2024-01-26 update readme to have photos of the pcb design
2024-01-27 make separate folder for graphics library
    this is so that potential game code can be reused for production and simulation without making any changes, with the code in the verilator directory only focusing on simulating the hardware the code 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
2024-01-27 change pico main file from C to C++
2024-01-27 begin to separate the 'game' code from the verilator simulation code
    so that the same main function can be used for simulation and production (running on pico) using placeholder functions to be defined for both, so what is being called depends on what's being compiled
2024-01-28 update pico code to utilize the common game code
2024-01-28 rename general function c++ files for clarity
2024-01-28 print help menu if no arguments provided
2024-01-29 create script to convert image file to a sprite
2024-02-01 allow 256 sprites to be generated from one single png file
    handled as part of compilation, src/util/sprites.png gets converted to a c array of sprites
2024-02-01 add font sprites for lowercase letters
2024-02-01 add new screenshot to readme featuring text display
2024-02-03 begin to make the spi queue thread safe
    i have noticed that occasionally the full data will not be sent between threads resulting in cut off sprites, and while this has not fixed the issue, its a good start
2024-02-08 continue to make things thread safe, but there are still bugs when tracing
